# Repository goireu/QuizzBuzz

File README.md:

# QuizzBuzz

Qwizzzzz Buzzzzz Weeeeezzzzzzz

This is a project to turn widespread ["got talent" like quiz buzzers](https://www.amazon.fr/RanDal-Buzzer-Alarme-Loterie-Lumi%C3%A8re/dp/B082Y17FFG) and an iOS-based device into a fun wireless quiz game.

Requirements:
- An iOS device (iPhone/iPad) with iOS 15+
- Spotify app installed on the device (a paid subscription is strongly recommended to avoid ads and allow for skipping songs)
- Some buzzers
- XCode for iOS 15+ for the Quizzer app
- KiCad for the PCB files
- nRF Connect SDK 1.9.1+ for the firmware

# Buzzer HowTo

Press the Buzzer for 3 to power it up, indicator will flash quickly while it isn't connected to a QuizzBuzz app.
When connection establishes the indicator will switch off.

After 30 seconds unconnected, the Buzzer will automatically power off.
After 30 minutes connected without buzzing, the Buzzer will also automatically power off.

# Game HowTo

When the game starts, everyone is allowed to buzz while the music is playing. The fastest buzzing team will have its buzzer blinking (much slower than when unconnected) and can try a guess.
If the guess is incorrect, and game is configured not to allow multiple answers, the indicator will stay lit and you can't buzz until next song.
Upon moving to next song, indicators will switch off and everyone can play again.

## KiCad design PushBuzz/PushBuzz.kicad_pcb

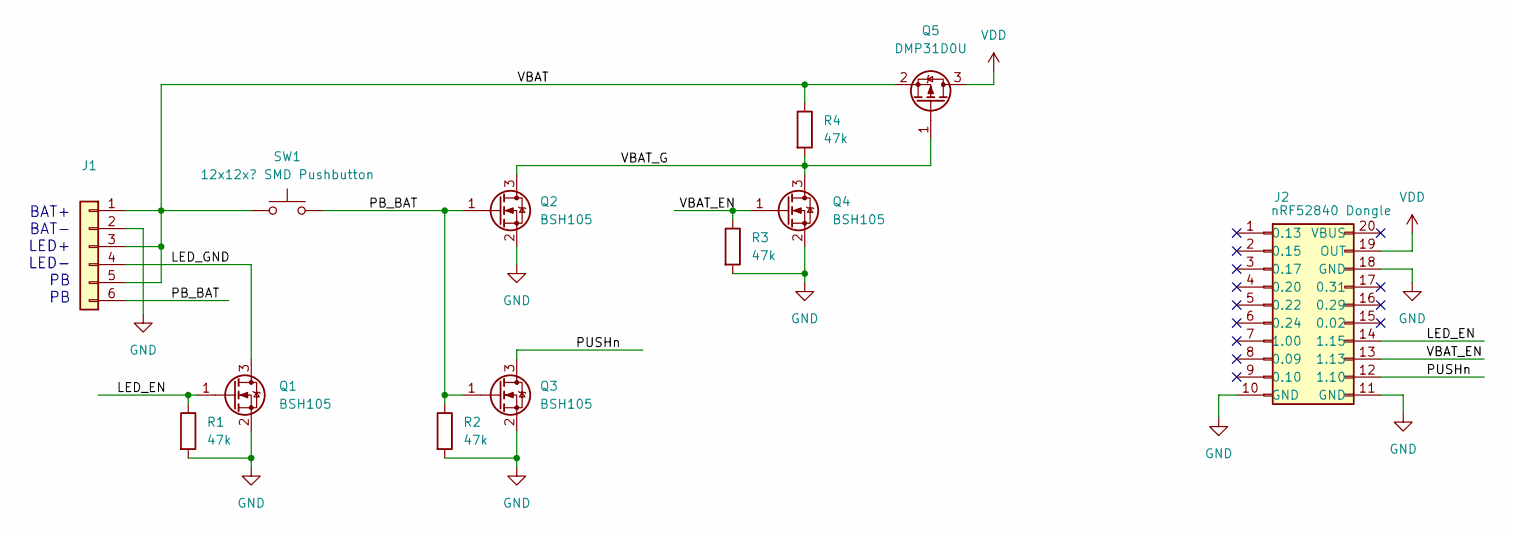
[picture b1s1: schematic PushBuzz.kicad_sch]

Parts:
J1: (no value)
J2: nRF52840 Dongle; nRF52840-Dongle
Q1, Q2, Q3, Q4: BSH105; SOT-23_Handsoldering
Q5: DMP31D0U; SOT-23_Handsoldering
R1, R2, R3, R4: 47k; R_0603_1608Metric_Pad0.98x0.95mm_HandSolder
SW1: 12x12x? SMD Pushbutton; 12x12 Pushbutton

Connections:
/LED_EN: J2.14 (1.15), Q1.1 (G), R1.1
/LED_GND: J1.4, Q1.3 (D)
/PB_BAT: J1.6, Q2.1 (G), Q3.1 (G), R2.1, SW1.2
/PUSHn: J2.12 (1.10), Q3.3 (D)
/VBAT: J1.1, J1.3, J1.5, Q5.2 (S), R4.1, SW1.1
/VBAT_EN: J2.13 (1.13), Q4.1 (G), R3.1
/VBAT_G: Q2.3 (D), Q4.3 (D), Q5.1 (G), R4.2
GND: J1.2, J2.10 (GND), J2.11 (GND), J2.18 (GND), Q1.2 (S), Q2.2 (S), Q3.2 (S), Q4.2 (S), R1.2, R2.2, R3.2
VDD: J2.19 (OUT), Q5.3 (D)

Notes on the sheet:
BAT+ BAT- LED+ LED- PB PB

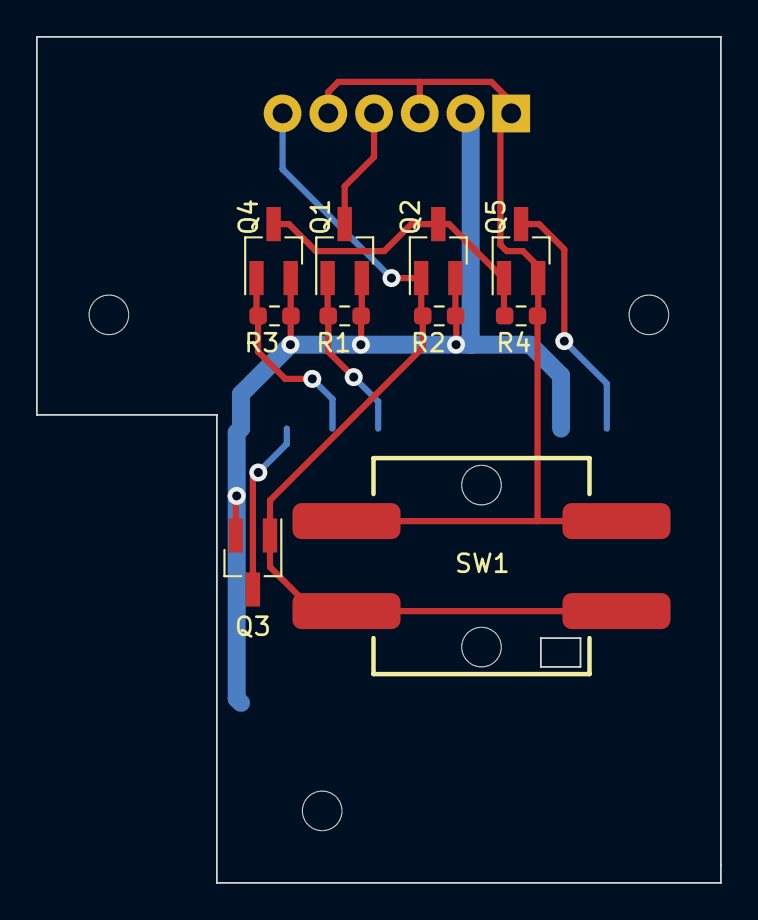
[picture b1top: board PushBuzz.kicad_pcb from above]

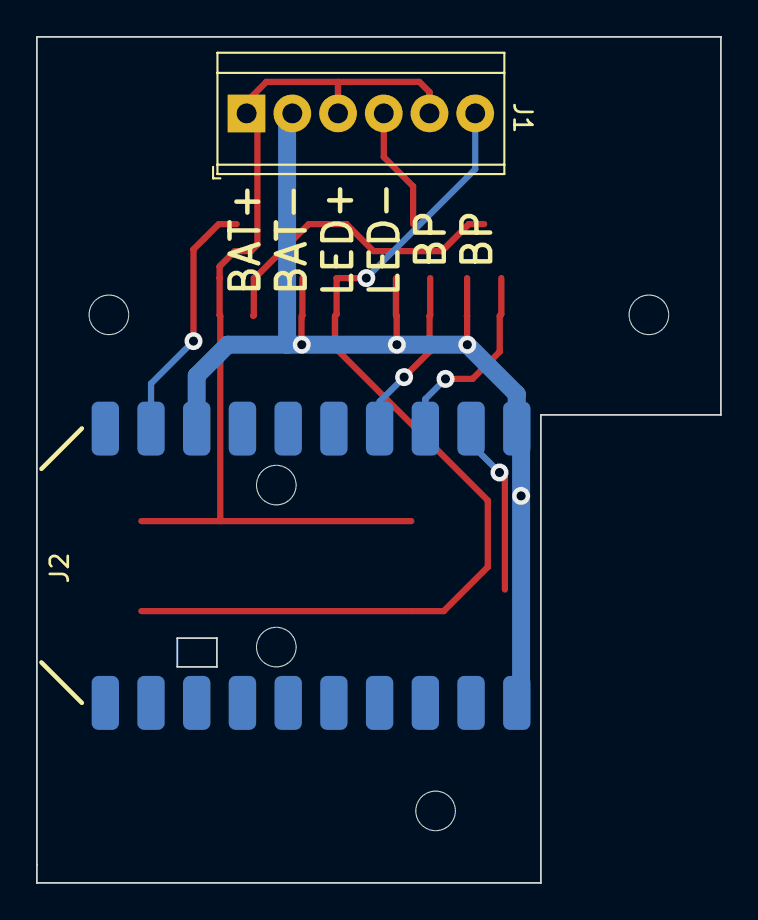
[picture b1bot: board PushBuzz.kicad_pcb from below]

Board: 2 copper layers, 38.0 x 47.0 mm, 12 parts (2 on the bottom side), 9 nets.

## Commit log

2022-04-13 PCB v1
2022-04-13 Firmware v1
2022-04-14 App v1
2022-04-22 BtLogic not needed anymore
2022-04-22 Improve git ignore tree
2022-04-27 Add support for complex LED indications
    Includes:
    - BT disconnected
    - Buzzer can't play
    - Buzzer selected
2022-05-11 Add alternate references
2022-05-11 Add support for power switch
    Also adjust coding style
2022-05-11 Add requirements to README
2022-05-15 Add new jingles
2022-05-15 Sort jingles in list
2022-08-04 Normalize jingles
2022-08-04 Prevent infinite loop rebooting for not-yet-patched modules
2022-08-04 Improve BLE range
2022-08-04 Implement handicap feature (yet to be tested)
2022-08-04 Fixes some bug I don't recall with phone in silent mode
2022-08-04 Some cleanup here
2022-08-05 Moved remote in viewModel
2022-08-05 display delay in buzzers config
2022-08-05 Improve answer view with more options
2022-10-15 Improved answer form, longer handicap, added buzz count statistic
2022-10-16 Add an MQTT score publisher... Yay!
2022-10-16 Added web scoreboard
2022-10-16 Update git ignore
2022-10-18 Removed webdash due to previous wrong manipulation
2022-10-18 Re-add webdash properly
2022-10-18 Add deploy script
2024-11-25 Update gitignore
